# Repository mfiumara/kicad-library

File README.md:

# KiCad Personal Library

A well-organized, category-based KiCad library following official KLC (KiCad Library Convention) standards. This library contains symbols, footprints, and 3D models for microcontrollers, wireless modules, connectors, analog ICs, and more.

## Quick Start

### 1. Clone the Repository

```bash
git clone <your-repo-url> ~/kicad-library
cd ~/kicad-library
git submodule update --init --recursive
```

### 2. Configure KiCad

Open KiCad and navigate to **Preferences → Configure Paths**. Add these environment variables:

| Variable | Path |
|---|---|
| `KICAD_PERSONAL_SYMBOL_DIR` | `/path/to/kicad-library/libraries/symbols` |
| `KICAD_PERSONAL_FOOTPRINT_DIR` | `/path/to/kicad-library/libraries/footprints` |
| `KICAD_PERSONAL_3DMODEL_DIR` | `/path/to/kicad-library/libraries/3dmodels` |
| `KICAD_PERSONAL_DATASHEET_DIR` | `/path/to/kicad-library/libraries/datasheets` |

### 3. Add Libraries to KiCad

**Symbols:** Preferences → Manage Symbol Libraries → Add library → Select `.kicad_sym` files from `libraries/symbols/`

**Footprints:** Preferences → Manage Footprint Libraries → Add library → Select `.pretty` folders from `libraries/footprints/`

See [docs/SETUP.md](docs/SETUP.md) for detailed configuration instructions.

## Library Contents

### Components

- **Microcontrollers:** ESP32 family (30+ variants), RP2040/Raspberry Pi Pico
- **RF/Wireless:** Nordic nRF5340
- **Analog ICs:** DACs, ADCs, op-amps
- **Connectors:** Headers, audio jacks, USB, specialized connectors

### Statistics

- **Symbols:** 33+ components across 4 categories
- **Footprints:** 55+ footprints
- **3D Models:** 37+ models (STEP format)
- **Projects:** 3 reference designs
- **Templates:** Schematic and PCB templates

## Repository Structure

```
kicad/
├── libraries/              # Main library content
│   ├── symbols/           # Symbol libraries (.kicad_sym)
│   │   ├── Microcontroller.kicad_sym
│   │   ├── RF_Wireless.kicad_sym
│   │   ├── Connectors.kicad_sym
│   │   └── Analog.kicad_sym
│   ├── footprints/        # Footprint libraries (.pretty)
│   │   ├── Microcontroller.pretty/
│   │   ├── RF_Wireless.pretty/
│   │   ├── Connectors.pretty/
│   │   └── Analog.pretty/
│   ├── 3dmodels/          # 3D models (.3dshapes)
│   │   ├── Microcontroller.3dshapes/
│   │   ├── RF_Wireless.3dshapes/
│   │   ├── Connectors.3dshapes/
│   │   └── Analog.3dshapes/
│   └── datasheets/        # Component datasheets
│       ├── Microcontroller/
│       ├── RF_Wireless/
│       ├── Connectors/
│       ├── Analog/
│       └── INDEX.md
│
├── submodules/            # External libraries (git submodules)
│   └── AudioJacks/        # Audio jack connector library
│
├── templates/             # Project templates
│   ├── schematic_templates/
│   ├── pcb_templates/
│   └── README.md
│
├── projects/              # Reference designs
│   ├── co2-sensor/        # ESP32-based CO2 sensor
│   ├── debughub/          # Debug interface board
│   ├── eurorack-templates/  # Eurorack module templates
│   └── README.md
│
└── docs/                  # Documentation
    ├── SETUP.md           # KiCad configuration guide
    ├── ORGANIZATION.md    # Library organization explained
    ├── CONTRIBUTING.md    # How to add components
    ├── NAMING_CONVENTIONS.md  # Naming standards
    ├── WORKFLOW.md        # Development workflow
    └── KLC_COMPLIANCE.md  # KiCad Library Convention compliance
```

## Featured Components

### Microcontrollers

- **Espressif ESP32 Family**
  - ESP32-WROOM-32 (WiFi & Bluetooth Classic)
  - ESP32-C3-MINI-1 (RISC-V, WiFi & BLE)
  - ESP32-S3-WROOM-1 (WiFi & Bluetooth 5 LE)
  - 30+ module variants

- **Raspberry Pi**
  - RP2040 microcontroller
  - Raspberry Pi Pico 2 W (THT and SMD variants)

### RF & Wireless

- Nordic nRF5340 (Bluetooth 5.3, Thread, Zigbee)

### Analog

- TI DAC80508 (8-channel 16-bit DAC with SPI)

### Connectors

- Audio jacks (3.5mm, 6.35mm) via AudioJacks submodule
- Relay connectors
- Standard headers and interface connectors

## Organization Philosophy

This library uses **category-based organization** following the official KiCad Library Convention (KLC):

- Components grouped by **function** (not manufacturer)
- Easier to find similar components
- Better for component substitution
- Scales well as library grows
- Aligned with KiCad official libraries

See [docs/ORGANIZATION.md](docs/ORGANIZATION.md) for detailed rationale.

## Documentation

- **[SETUP.md](docs/SETUP.md)** - Complete KiCad configuration guide
- **[ORGANIZATION.md](docs/ORGANIZATION.md)** - Library organization explained
- **[CONTRIBUTING.md](docs/CONTRIBUTING.md)** - How to add new components
- **[NAMING_CONVENTIONS.md](docs/NAMING_CONVENTIONS.md)** - Naming standards and conventions
- **[WORKFLOW.md](docs/WORKFLOW.md)** - Git workflow and development process
- **[KLC_COMPLIANCE.md](docs/KLC_COMPLIANCE.md)** - KiCad Library Convention standards

**Category Documentation:**
- [Symbol Library Index](libraries/symbols/README.md)
- [Footprint Library Index](libraries/footprints/README.md)
- [3D Model Index](libraries/3dmodels/README.md)
- [Datasheet Index](libraries/datasheets/INDEX.md)
- [Submodules Guide](submodules/README.md)
- [Projects Overview](projects/README.md)
- [Templates Guide](templates/README.md)

## Contributing

Contributions are welcome! To add new components:

1. Read [CONTRIBUTING.md](docs/CONTRIBUTING.md) for guidelines
2. Follow [NAMING_CONVENTIONS.md](docs/NAMING_CONVENTIONS.md) for naming
3. Ensure [KLC_COMPLIANCE.md](docs/KLC_COMPLIANCE.md) standards are met
4. Test in a real project before submitting
5. Update relevant documentation

See [WORKFLOW.md](docs/WORKFLOW.md) for git workflow and development process.

## Standards and Compliance

This library follows:

- **KiCad Library Convention (KLC)** - Official KiCad standards
- **IPC-7351** - Footprint naming for generic packages
- **Category-based organization** - Components grouped by function
- **Environment variables** - Portable library paths
- **Git submodules** - For external library management

All components are validated for:
- Correct symbol pin properties
- Accurate footprint dimensions
- Proper 3D model alignment
- Complete documentation

## Projects

The `projects/` directory contains reference designs:

- **co2-sensor** - ESP32-based environmental monitoring
- **debughub** - Universal debug interface board
- **eurorack-templates** - Synthesizer module templates

These projects demonstrate library usage and serve as templates for new designs.

## Submodules

External libraries are managed as git submodules:

- **AudioJacks** - Comprehensive audio jack connector library from [clacktronics](https://github.com/clacktronics/AudioJacks)

To initialize submodules after cloning:

```bash
git submodule update --init --recursive
```

See [submodules/README.md](submodules/README.md) for management details.

## Quick Reference

### Finding Components

| Component Type | Symbol Library | Footprint Library |
|---|---|---|
| ESP32, RP2040 | Microcontroller | Microcontroller.pretty |
| nRF5340, wireless | RF_Wireless | RF_Wireless.pretty |
| DAC, ADC, op-amps | Analog | Analog.pretty |
| Headers, jacks | Connectors | Connectors.pretty |

### File Naming

- **Symbols:** `ManufacturerPrefix_PartNumber` (e.g., `ESP32-WROOM-32`)
- **Footprints:** `PartNumber.kicad_mod` or `PackageCode.kicad_mod`
- **3D Models:** `FootprintName.step` (matches footprint name)

See [NAMING_CONVENTIONS.md](docs/NAMING_CONVENTIONS.md) for complete guidelines.

## Version Control

This repository uses:

- **Main branch:** Stable, tested components
- **Feature branches:** For development and testing
- **Git submodules:** For external library management
- **.gitignore:** Excludes KiCad backups, OS files, build artifacts
- **.gitattributes:** Ensures correct line endings for KiCad files

## Requirements

- **KiCad 7.0 or later** (recommended: KiCad 8.0+)
- **Git** for version control and submodule management
- **~50MB disk space** for complete library with 3D models

## Getting Help

- **Setup issues:** See [SETUP.md](docs/SETUP.md)
- **Library organization questions:** See [ORGANIZATION.md](docs/ORGANIZATION.md)
- **Adding components:** See [CONTRIBUTING.md](docs/CONTRIBUTING.md)
- **Naming questions:** See [NAMING_CONVENTIONS.md](docs/NAMING_CONVENTIONS.md)
- **Git workflow:** See [WORKFLOW.md](docs/WORKFLOW.md)

## License

This library is for personal use. Individual components may have different licenses:
- Components created by me: Free to use
- Submodules (AudioJacks): Check respective repository licenses
- Manufacturer-provided 3D models: Subject to manufacturer terms

## Acknowledgments

- **KiCad** - Open-source EDA software
- **Espressif** - ESP32 resources and documentation
- **Raspberry Pi Foundation** - RP2040 resources
- **Nordic Semiconductor** - nRF5340 resources
- **clacktronics** - AudioJacks library
- **KiCad community** - Guidelines and best practices

---

**Last Updated:** December 2024
**KiCad Version:** 7.0+
**Library Version:** 2.0.0 (reorganized structure)

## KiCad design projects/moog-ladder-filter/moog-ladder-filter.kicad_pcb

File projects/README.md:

# Projects

This directory contains reference projects and design examples that use the component libraries in this repository.

## Purpose

These projects serve multiple roles:

1. **Reference Designs** - Working examples of how to use library components
2. **Test Cases** - Verify that library changes don't break existing designs
3. **Templates** - Starting points for similar projects
4. **Documentation** - Practical examples of component usage

## Projects

### co2-sensor/

CO2 sensor project with multiple design variants.

**Description:**
Environmental monitoring device measuring CO2 concentration, temperature, and humidity.

**Variants:**

#### no-ai/ - Original Design
- **Main Board:** ESP32-based CO2 sensor
- **Key Components:**
  - ESP32-WROOM-32 (WiFi/BT connectivity)
  - CO2 sensor (NDIR or equivalent)
  - Temperature/humidity sensor
  - Power supply circuitry
  - Display interface (optional)

- **Features:**
  - WiFi connectivity for data logging
  - Local data display
  - Battery or USB powered
  - ESPHome integration ready

#### ai/ - AI-Assisted Variant
- **Location:** `ai/hardware/pcb/`
- **Files:**
  - co2-sensor-adapter.kicad_pro
  - co2-sensor-adapter.kicad_sch
  - co2-sensor-adapter.kicad_pcb

- **Purpose:** Adapter board for CO2 sensor with AI-assisted design workflow
- **ESPHome:** Configuration in `ai/.esphome/` directory

**Status:** Active development

**Library Dependencies:**
- Microcontroller: ESP32-WROOM-32
- Connectors: Various headers
- Power: Voltage regulators

### debughub/

Debug interface board for embedded development.

**Description:**
Universal debug hub for microcontroller development and testing.

**Main Board:** `Untitled/`
- Untitled.kicad_pro
- Untitled.kicad_sch
- Untitled.kicad_pcb

**Features:**
- JTAG/SWD interface
- UART connections
- Logic level translation
- Power supply options
- LED indicators

**Status:** In development

**Library Dependencies:**
- Connectors: Debug headers, USB
- Interface ICs: Level shifters
- Power: Regulators

### eurorack-templates/

Eurorack synthesizer module templates (originally from separate repository).

**Description:**
Comprehensive templates for Eurorack modular synthesizer module design.

**Origin:** https://github.com/[original-repo] (git submodule history)

**Contents:**

#### Front Panels
- **1HP** - 1 unit wide panel template
- **2HP** - 2 unit wide panel template
- **4HP** - 4 unit wide panel template
- **8HP** - 8 unit wide panel template
- **10HP** - 10 unit wide panel template
- **12HP** - 12 unit wide panel template

#### Connector Panels
- **12HP** - Standard and 100mm deep variants

#### Main Boards
- **12HP** - Main board template with power connector

**Features:**
- Correct Eurorack dimensions (1HP = 5.08mm)
- Standard mounting hole positions
- Power connector templates (10-pin or 16-pin)
- Front panel component placement guides

**Status:** Template collection

**Library Dependencies:**
- Connectors: Eurorack power connectors, audio jacks (AudioJacks submodule)
- Components: Op-amps, buffers (when populated)

## Using These Projects

### As References

1. Open project in KiCad
2. Review schematic for component usage examples
3. Check PCB layout for best practices
4. Examine bill of materials (BOM)

### As Templates

1. Copy entire project directory
2. Rename all files to your project name
3. Modify schematic and PCB for your needs
4. Update library references if needed

### For Testing

Before committing library changes:

1. Open each project
2. Verify components still load correctly
3. Check for missing footprints or 3D models
4. Run DRC (Design Rules Check)
5. Run ERC (Electrical Rules Check)
6. Fix any issues before committing library changes

## Project Structure

Standard project structure:

```
project-name/
├── project-name.kicad_pro      # Project file
├── project-name.kicad_sch      # Schematic
├── project-name.kicad_pcb      # PCB layout
├── README.md                   # Project documentation
├── bom/                        # Bill of materials
├── gerbers/                    # Manufacturing files
├── datasheets/                 # Project-specific datasheets
└── docs/                       # Assembly instructions, etc.
```

## Library Paths

Projects use relative paths to reference the main library:

**Symbols:**
```
${KIPRJMOD}/../../libraries/symbols/CategoryName.kicad_sym
```

**Footprints:**
```
${KIPRJMOD}/../../libraries/footprints/CategoryName.pretty
```

**3D Models:**
Referenced via `KICAD_PERSONAL_3DMODEL_DIR` environment variable or relative paths.

## Adding New Projects

When adding a new project to this directory:

1. **Create project directory:**
   ```bash
   mkdir projects/new-project
   cd projects/new-project
   ```

2. **Design your project** using libraries from this repository

3. **Configure library paths** to use relative paths when possible:
   - Use `${KIPRJMOD}/../../libraries/...` for portability

4. **Add project documentation:**
   - Create README.md with:
     - Project description
     - Key features
     - Components used
     - Build instructions (if applicable)
     - Status (prototype, tested, production, etc.)

5. **Test thoroughly:**
   - Verify all components load
   - Run DRC/ERC
   - Generate gerbers successfully
   - Test 3D view

6. **Update this README** with project entry

7. **Commit with clear message:**
   ```bash
   git add projects/new-project
   git commit -m "Add new-project: [brief description]"
   ```

## Project Guidelines

### File Organization

- Keep all project files together in one directory
- Use consistent naming (all files named after project)
- Separate manufacturing files (gerbers/) from source files
- Include README for each project

### Library Usage

- Use components from this library when possible
- Document any external library dependencies
- Test that library changes don't break project
- Report issues with library components

### Documentation

Each project should include:

- **README.md** - Overview, features, status
- **Schematic PDF** (exported from KiCad)
- **BOM** - Bill of materials (CSV or Excel)
- **Assembly notes** - Special instructions
- **Photos** - If built, include photos

### Version Control

- Commit working versions frequently
- Tag releases (v1.0, v1.1, etc.)
- Document changes in project README
- Don't commit gerbers to git (generate as needed)
- Don't commit backups or temp files (use .gitignore)

## Common Workflows

### Starting a New Project

1. Copy an existing similar project as template
2. Rename all files
3. Open in KiCad
4. Clear schematic and PCB (keep project settings)
5. Design your circuit

### Updating Library References

If library structure changes:

1. Open project in KiCad
2. **Preferences → Manage Symbol Libraries**
3. Update paths to point to new library locations
4. **Preferences → Manage Footprint Libraries**
5. Update footprint library paths
6. Verify all components still load

### Exporting for Manufacturing

1. Generate Gerbers: **File → Plot**
2. Generate Drill files: **File → Fabrication Outputs → Drill Files**
3. Generate BOM: **Tools → Generate BOM**
4. Export assembly drawings: **File → Plot** (assembly layer)
5. Export Pick & Place: **File → Fabrication Outputs → Component Placement**

## Project Status Legend

- **Prototype** - Initial design, not tested
- **Testing** - Built and under testing
- **Working** - Tested and functional
- **Production** - Proven design, ready for manufacture
- **Archived** - Old project, kept for reference

## Troubleshooting

### Components Missing

- Verify library paths are correct
- Check that library files exist
- Update library references if structure changed
- See [SETUP.md](../docs/SETUP.md) for configuration

### DRC/ERC Errors After Library Update

- Review library changes
- Update footprints if pins changed
- Check for renamed components
- Verify electrical rules still apply

### 3D Models Don't Load

- Set `KICAD_PERSONAL_3DMODEL_DIR` environment variable
- Check 3D model paths in footprints
- Verify 3D model files exist

## Questions?

- See [SETUP.md](../docs/SETUP.md) for KiCad configuration
- See [ORGANIZATION.md](../docs/ORGANIZATION.md) for library structure
- See [CONTRIBUTING.md](../docs/CONTRIBUTING.md) for adding projects

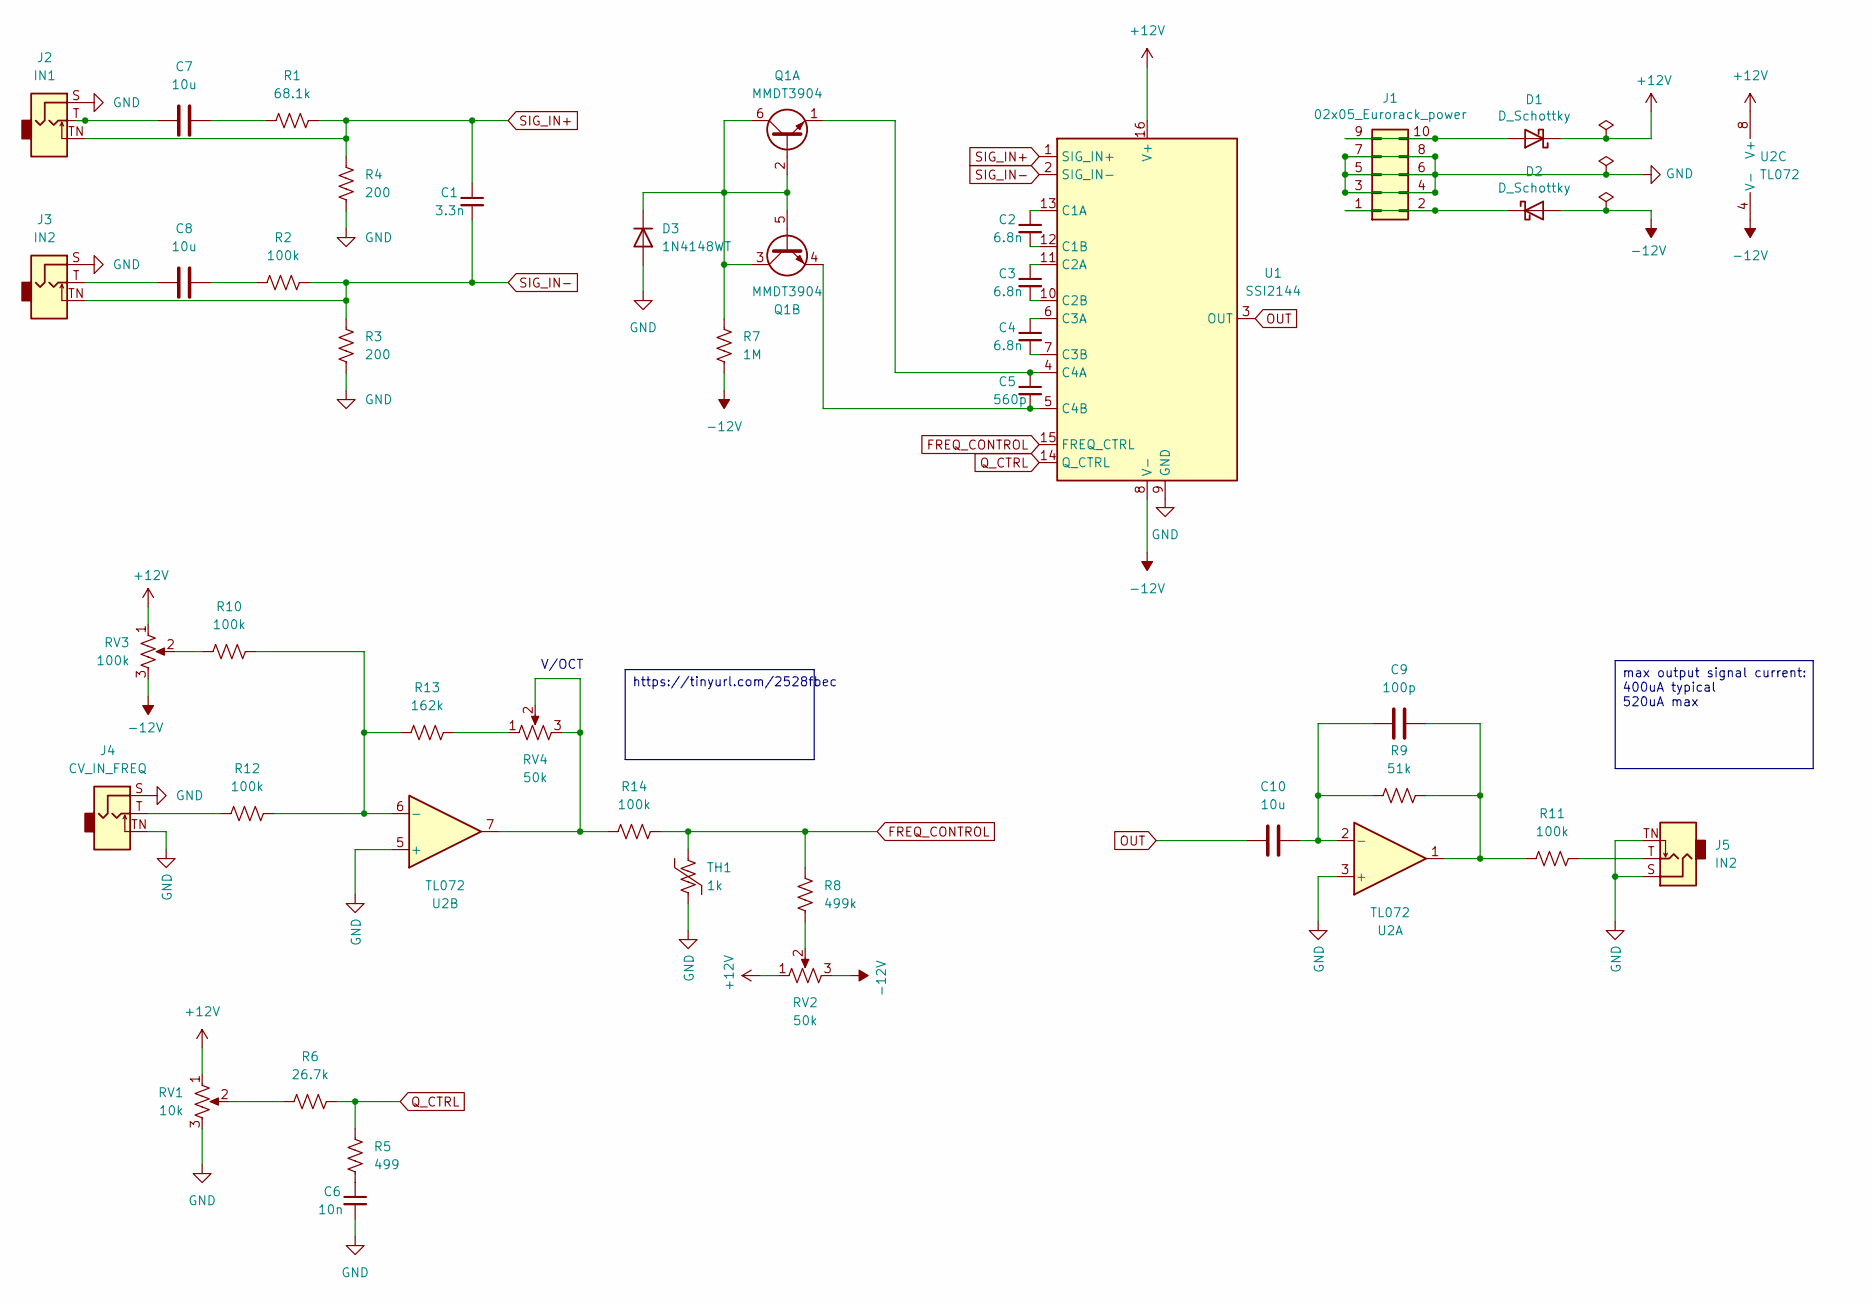
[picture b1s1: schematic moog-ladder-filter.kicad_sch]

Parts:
C1: 3.3n; C_0805_2012Metric
C2, C3, C4: 6.8n; C_0805_2012Metric
C5: 560p; C_0805_2012Metric
C6: 10n; C_0805_2012Metric
C7, C8, C10: 10u; C_0805_2012Metric
C9: 100p; C_0805_2012Metric
D1, D2: D_Schottky; D_SMA
D3: 1N4148WT; D_SOD-523
J1: 02x05_Eurorack_power; IDC-Header_2x05_P2.54mm_Vertical
J2: IN1; Jack_3.5mm_QingPu_WQP-PJ301M-12_Vertical
J3, J5: IN2; Jack_3.5mm_QingPu_WQP-PJ301M-12_Vertical
J4: CV_IN_FREQ; Jack_3.5mm_QingPu_WQP-PJ301M-12_Vertical
Q1: MMDT3904; SOT-363_SC-70-6
R1: 68.1k; R_0805_2012Metric
R2, R10, R11, R12, R14: 100k; R_0805_2012Metric
R3, R4: 200; R_0805_2012Metric
R5: 499; R_0805_2012Metric
R6: 26.7k; R_0805_2012Metric
R7: 1M; R_0805_2012Metric
R8: 499k; R_0805_2012Metric
R9: 51k; R_0805_2012Metric
R13: 162k; R_0805_2012Metric
RV1: 10k; RD901F4015FA100K00DL1
RV2, RV4: 50k; 3296W1503LF
RV3: 100k; RD901F4015FA100K00DL1
TH1: 1k; RESC1608X55N
U1: SSI2144; SSOP-16_3.9x4.9mm_P0.635mm
U2: TL072; SOIC127P600X175-8N

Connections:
+12V: D1.1 (K), RV1.1, RV2.1, RV3.1, U1.16 (V+), U2.8 (V+)
-12V: D2.2 (A), R7.2, RV2.3, RV3.3, U1.8 (V-), U2.4 (V-)
FREQ_CONTROL: R8.1, R14.2, TH1.1, U1.15 (FREQ_CTRL)
GND: C6.2, D3.2 (A), J1.3, J1.4, J1.5, J1.6, J1.7, J1.8, J2.S, J3.S, J4.S, J4.TN, J5.S, J5.TN, R3.1, R4.1, RV1.3, TH1.2, U1.9 (GND), U2.3 (+), U2.5 (+)
unnamed: C6.1, R5.1
unnamed: C7.1, J2.T
unnamed: C7.2, R1.1
unnamed: C8.1, J3.T
unnamed: C8.2, R2.1
unnamed: C9.2, R9.2, R11.1, U2.1
unnamed: D1.2 (A), J1.9, J1.10
unnamed: D2.1 (K), J1.1, J1.2
unnamed: D3.1 (K), Q1.2 (B1), Q1.3 (C2), Q1.5 (B2), Q1.6 (C1), R7.1
unnamed: J4.T, R12.1
unnamed: J5.T, R11.2
unnamed: C5.1, Q1.1 (E1), U1.4 (C4A)
unnamed: C5.2, Q1.4 (E2), U1.5 (C4B)
unnamed: R6.2, RV1.2
unnamed: R8.2, RV2.2
unnamed: R10.1, RV3.2
unnamed: R13.2, RV4.1
unnamed: R14.1, RV4.2, RV4.3, U2.7
unnamed: C2.1, U1.13 (C1A)
unnamed: C2.2, U1.12 (C1B)
unnamed: C3.1, U1.11 (C2A)
unnamed: C3.2, U1.10 (C2B)
unnamed: C4.1, U1.6 (C3A)
unnamed: C4.2, U1.7 (C3B)
unnamed: C9.1, C10.2, R9.1, U2.2 (-)
unnamed: R10.2, R12.2, R13.1, U2.6 (-)
OUT: C10.1, U1.3 (OUT)
Q_CTRL: R5.2, R6.1, U1.14 (Q_CTRL)
SIG_IN+: C1.1, J2.TN, R1.2, R4.2, U1.1 (SIG_IN+)
SIG_IN-: C1.2, J3.TN, R2.2, R3.2, U1.2 (SIG_IN-)

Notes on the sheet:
V/OCT
max output signal current: 400uA typical 520uA max
https://tinyurl.com/2528fbec

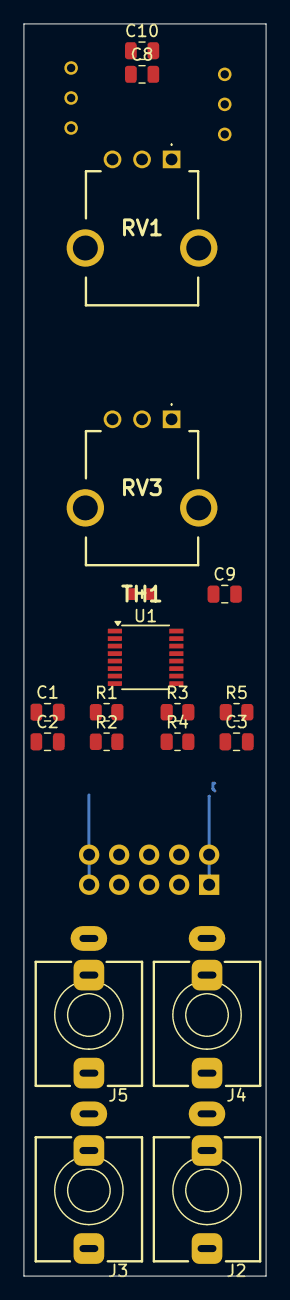
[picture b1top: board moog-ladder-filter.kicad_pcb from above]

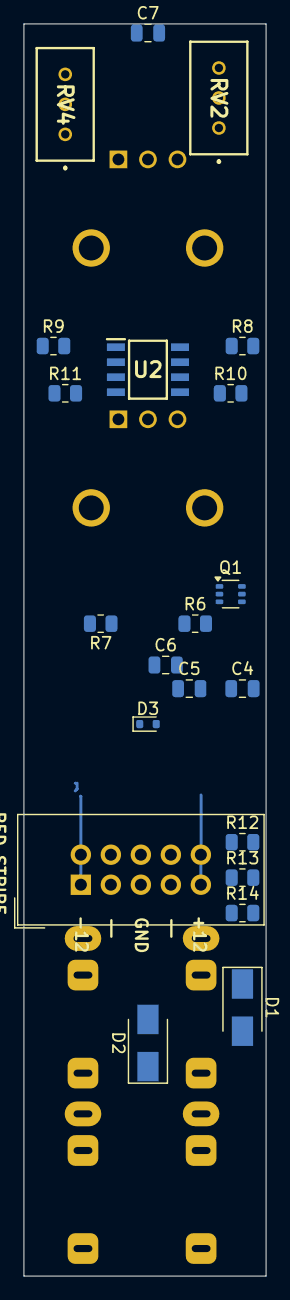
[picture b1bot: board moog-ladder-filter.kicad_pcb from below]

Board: 4 copper layers, 20.5 x 106.0 mm, 40 parts (21 on the bottom side), 34 nets.

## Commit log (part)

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2024-04-30 wip: initial readme docs
2024-04-30 update symbol libs
2025-12-09 add some libs
2025-12-15 reorganzie folders
2026-01-25 wip: update
2026-01-26 maint: remove old lib files
2026-01-26 feat: add MKS2 wima coupling cap
2026-01-26 maint: add all parts into eurorack library
2026-01-26 feat: Add Yageo RC series resistors
2026-01-26 feat: C values
2026-03-25 update routing using AI
